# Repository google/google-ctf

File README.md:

# Google CTF

This repository lists most of the challenges used in the Google CTF since 2017, as well as most of the infrastructure that can be used to run them. **IMPORTANT** - The code in the 201x and 202x folders have unfixed security vulnerabilities. These are there on purpose, and running these on real production infrastructure is not safe.

Read more about the Google CTF here: https://security.googleblog.com/2017/06/announcing-google-capture-flag-2017.html

Note this is not an official Google product.

### License

The google-ctf project is available as open source under the terms of the [Apache-2.0 license](https://github.com/google/google-ctf/blob/master/LICENSE).

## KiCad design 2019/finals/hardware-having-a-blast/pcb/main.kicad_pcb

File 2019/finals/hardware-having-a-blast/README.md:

# name: "Having a Blast"

description: Never open strange boxes without a permit. https://youtu.be/_8fBHnH4VNE

The Video above contains no hint or flag that you need to hunt for. This is a time scheduled challenge.

Challenge rules are available https://docs.google.com/document/d/1H1iL3Lq8BtMJRlrBNAAG3CYmMLnWO6IFaZPt1xe8dxI/edit?usp=sharing

# flag: "CTF{k33p-t4k1ng-pl3as3}"

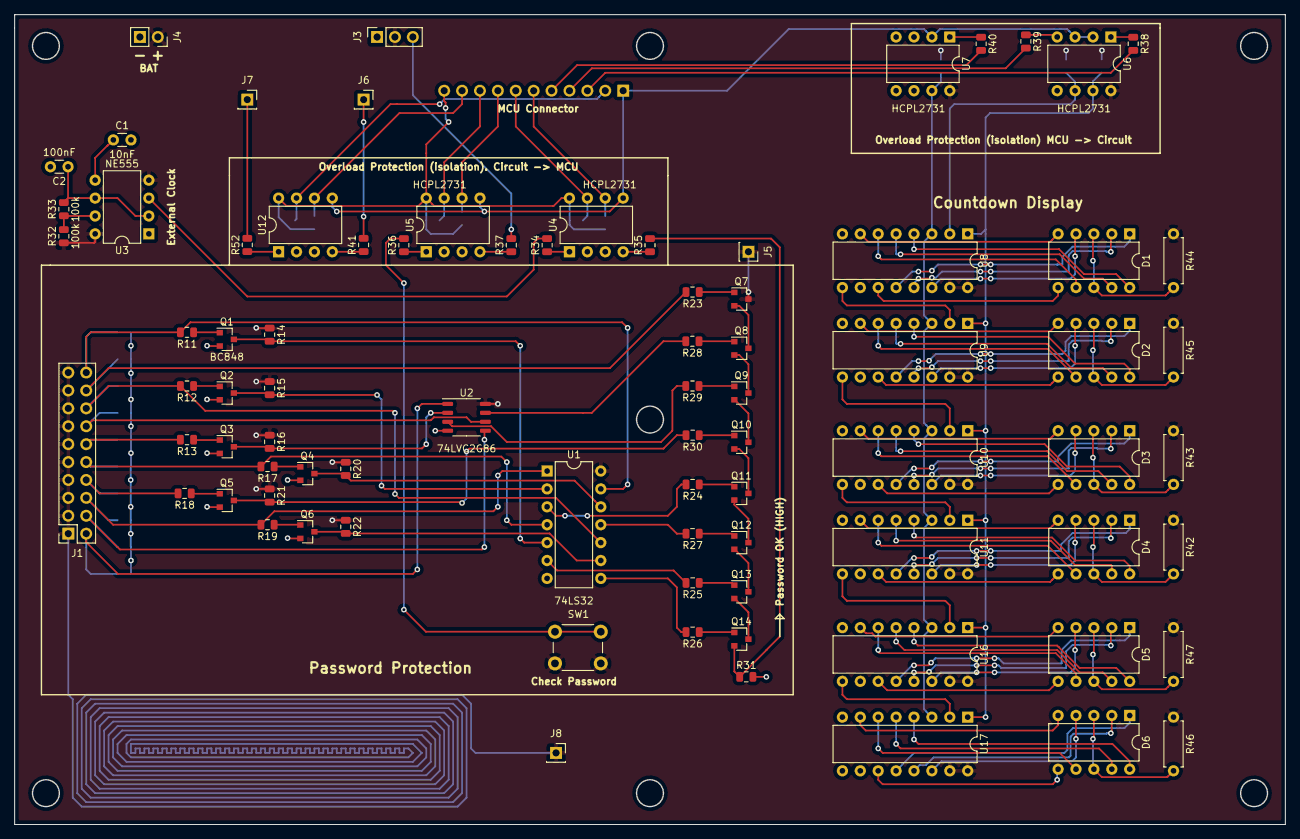
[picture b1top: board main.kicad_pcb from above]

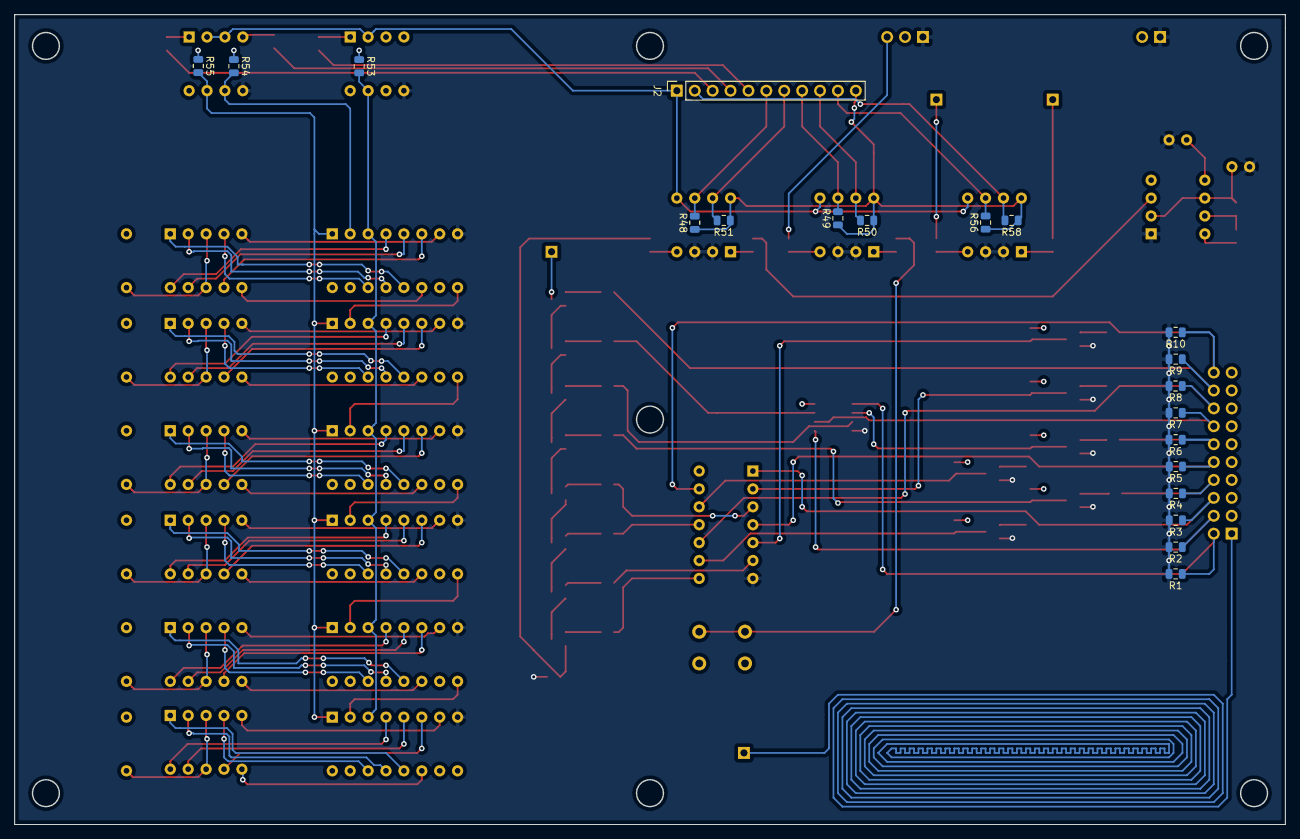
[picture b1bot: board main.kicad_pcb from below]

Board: 4 copper layers, 180.3 x 114.9 mm, 102 parts (20 on the bottom side), 136 nets.

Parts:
C1: 10nF; C_Disc_D3.0mm_W1.6mm_P2.50mm
C2: 100nF; C_Disc_D3.0mm_W1.6mm_P2.50mm
D1, D2, D3, D4, D5, D6: TDSR1050; DIP-10_W7.62mm
J1: Conn_02x10_Odd_Even; PinSocket_2x10_P2.54mm_Vertical
J2: Conn_01x11; PinSocket_1x11_P2.54mm_Vertical
J3: Conn_01x03; PinSocket_1x03_P2.54mm_Vertical
J4: Conn_01x02_Male; PinSocket_1x02_P2.54mm_Vertical
J5, J6, J7, J8: Conn_01x01_Male; PinSocket_1x01_P2.54mm_Vertical
Q1, Q2, Q3, Q4, Q5, Q6, Q7, Q8, Q9, Q10, Q11, Q12, Q13, Q14: BC848; SOT-23
R1, R2, R3, R4, R5, R6, R7, R8, R9, R10, R11, R12, R13, R17, R18, R19, R23, R24, R25, R26, R27, R28, R29, R30: 10k; R_0805_2012Metric
R14, R15, R16, R20, R21, R22, R31, R48, R49, R50, R51, R53, R54, R55, R56, R58: 1k; R_0805_2012Metric
R32, R33: 100k; R_0805_2012Metric
R34, R35, R36, R37, R38, R39, R40, R41, R52: 510; R_0805_2012Metric
R42, R43, R44, R45, R46, R47: 3k; R_Axial_DIN0207_L6.3mm_D2.5mm_P7.62mm_Horizontal
SW1: SW_Push; SW_PUSH_6mm
U1: 74LS32; DIP-14_W7.62mm
U2: 74LVC2G86; SSOP-8_3.9x5.05mm_P1.27mm
U3: NE555; DIP-8_W7.62mm
U4, U5, U6, U7, U12: HCPL2731; DIP-8_W7.62mm
U8, U9, U10, U11, U16, U17: CD4094B; DIP-16_W7.62mm

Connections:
/A0: J1.2, R1.1, U2.1
/A1: J1.4, R2.1, U2.5
/A2: J1.6, R3.1, R19.2, U1.1
/A3: J1.8, R4.1, R18.2
/A4: J1.10, R5.1, R17.2, U1.4
/B0: J1.12, R6.1, R13.2
/B1: J1.14, R7.1, U2.6
/B2: J1.16, R8.1, R12.2, U1.10
/B3: J1.18, R9.1, R23.2
/B4: J1.20, R10.1, R11.2, U1.13
/MCU_GND: J2.1, U4.5, U5.5, U6.2, U6.3, U7.2, U12.5
/MCU_VCC: J2.11, R48.1, R49.1, R50.1, R51.1, R56.1, R58.1, U4.8, U5.8, U12.8
/SevenSegments/Clock: R53.2, U7.7, U8.3, U9.3, U10.3, U11.3, U16.3, U17.3
/SevenSegments/Data: R54.2, U6.6, U8.2
/SevenSegments/Strobe: R55.2, U6.7, U8.1, U9.1, U10.1, U11.1, U16.1, U17.1
/logicIC/LogicOK: Q14.2, R31.1, R35.2
/logicIC/_40: R29.2, U2.3
/logicIC/_45: R28.2, U2.7
/logicIC/~A2: Q6.3, R22.2, U1.9
/logicIC/~A3: Q5.3, R21.2, R30.2
/logicIC/~A4: Q4.3, R20.2, U1.12
/logicIC/~B0: Q3.3, R16.2, U2.2
/logicIC/~B2: Q2.3, R15.2, U1.2
/logicIC/~B4: Q1.3, R14.2, U1.5
/wire_check: J7.1, R52.2
/wire_check2: J6.1, R41.2
GND: C1.2, C2.2, J3.1, J4.2, Q1.2, Q2.2, Q3.2, Q4.2, Q5.2, Q6.2, R1.2, R2.2, R3.2, R4.2, R5.2, R6.2, R7.2, R8.2, R9.2, R10.2, R31.2, U1.7, U2.4, U3.1, U4.2, U4.3, U5.2, U5.3, U6.5, U7.5, U8.8, U9.8, U10.8, U11.8, U12.2, U12.3, U16.8, U17.8
unnamed: C1.1, U3.5
unnamed: C2.1, R33.2, U3.2, U3.6
unnamed: D1.1, U8.12
unnamed: D1.2, U8.13
unnamed: D1.3, D1.8, R44.2
unnamed: D1.4, U8.14
unnamed: D1.5, U8.7
unnamed: D1.6, U8.11
unnamed: D1.7, U8.6
unnamed: D1.9, U8.5
unnamed: D1.10, U8.4
unnamed: D2.1, U9.12
unnamed: D2.2, U9.13
unnamed: D2.3, D2.8, R45.2
unnamed: D2.4, U9.14
unnamed: D2.5, U9.7
unnamed: D2.6, U9.11
unnamed: D2.7, U9.6
unnamed: D2.9, U9.5
unnamed: D2.10, U9.4
unnamed: D3.1, U10.12
unnamed: D3.2, U10.13
unnamed: D3.3, D3.8, R43.2
unnamed: D3.4, U10.14
unnamed: D3.5, U10.7
unnamed: D3.6, U10.11
unnamed: D3.7, U10.6
unnamed: D3.9, U10.5
unnamed: D3.10, U10.4
unnamed: D4.1, U11.12
unnamed: D4.2, U11.13
unnamed: D4.3, D4.8, R42.2
unnamed: D4.4, U11.14
unnamed: D4.5, U11.7
unnamed: D4.6, U11.11
unnamed: D4.7, U11.6
unnamed: D4.9, U11.5
unnamed: D4.10, U11.4
unnamed: D5.1, U16.12
unnamed: D5.2, U16.13
unnamed: D5.3, D5.8, R47.2
unnamed: D5.4, U16.14
unnamed: D5.5, U16.7
unnamed: D5.6, U16.11
unnamed: D5.7, U16.6
unnamed: D5.9, U16.5
unnamed: D5.10, U16.4
unnamed: D6.1, U17.12
unnamed: D6.2, U17.13
unnamed: D6.3, D6.8, R46.2
unnamed: D6.4, U17.14
unnamed: D6.5, U17.7
unnamed: D6.6, U17.11
unnamed: D6.7, U17.6
unnamed: D6.9, U17.5
unnamed: D6.10, U17.4
unnamed: J2.2, R58.2, U12.7
unnamed: J2.3, R38.2
unnamed: J2.4, R39.2
unnamed: J2.5, R40.2
unnamed: J2.6, R48.2, U4.6
unnamed: J2.7, R51.2, U4.7
unnamed: J2.8, R49.2, U5.6
unnamed: J2.9, R50.2, U5.7
unnamed: J2.10, R56.2, U12.6
unnamed: J3.3, R37.2
unnamed: Q1.1, R11.1
unnamed: Q2.1, R12.1
unnamed: Q3.1, R13.1
unnamed: Q4.1, R17.1
unnamed: Q5.1, R18.1
unnamed: Q6.1, R19.1
unnamed: Q7.1, R23.1
unnamed: Q7.2, Q8.3
unnamed: Q8.1, R28.1
unnamed: Q8.2, Q9.3
unnamed: Q9.1, R29.1
unnamed: Q10.1, R30.1
unnamed: Q10.2, Q11.3
unnamed: Q9.2, Q10.3
unnamed: Q11.1, R24.1
unnamed: Q11.2, Q12.3
unnamed: Q12.1, R27.1
unnamed: Q12.2, Q13.3
unnamed: Q13.1, R25.1
unnamed: Q13.2, Q14.3
unnamed: Q14.1, R26.1
unnamed: R24.2, U1.3
unnamed: R25.2, U1.6
unnamed: R26.2, U1.8
unnamed: R27.2, U1.11
unnamed: R32.2, R33.1, U3.7
unnamed: R34.1, U4.1
unnamed: R34.2, U3.3
unnamed: R35.1, U4.4
unnamed: R36.1, U5.1
unnamed: R36.2, SW1.2
unnamed: R37.1, U5.4
unnamed: R38.1, U6.1
unnamed: R39.1, U6.4
unnamed: R40.1, U7.1
unnamed: R41.1, U12.4
unnamed: R52.1, U12.1
unnamed: U8.9, U9.2
unnamed: U9.9, U10.2
unnamed: U10.9, U11.2
unnamed: U11.9, U16.2
unnamed: U16.9, U17.2
VCC: J1.1, J1.3, J1.5, J1.7, J1.9, J1.11, J1.13, J1.15, J1.17, J1.19, J3.2, J4.1, J5.1, J8.1, Q7.3, R14.1, R15.1, R16.1, R20.1, R21.1, R22.1, R32.1, R42.1, R43.1, R44.1, R45.1, R46.1, R47.1, R53.1, R54.1, R55.1, SW1.1, U1.14, U2.8, U3.4, U3.8, U6.8, U7.8, U8.15, U8.16, U9.15, U9.16, U10.15, U10.16, U11.15, U11.16, U16.15, U16.16, U17.15, U17.16

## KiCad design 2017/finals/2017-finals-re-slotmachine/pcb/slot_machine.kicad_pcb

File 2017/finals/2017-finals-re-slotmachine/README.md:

{

# name: Slot Machine 1
# description: We found some spare slot machines that are used at GenericCasinoCompany. We believe that there is some hidden treasure inside, can you find it?

# flag: CTF{5UP3R_53CR37_BTN_C0MB1N4710N}"

}

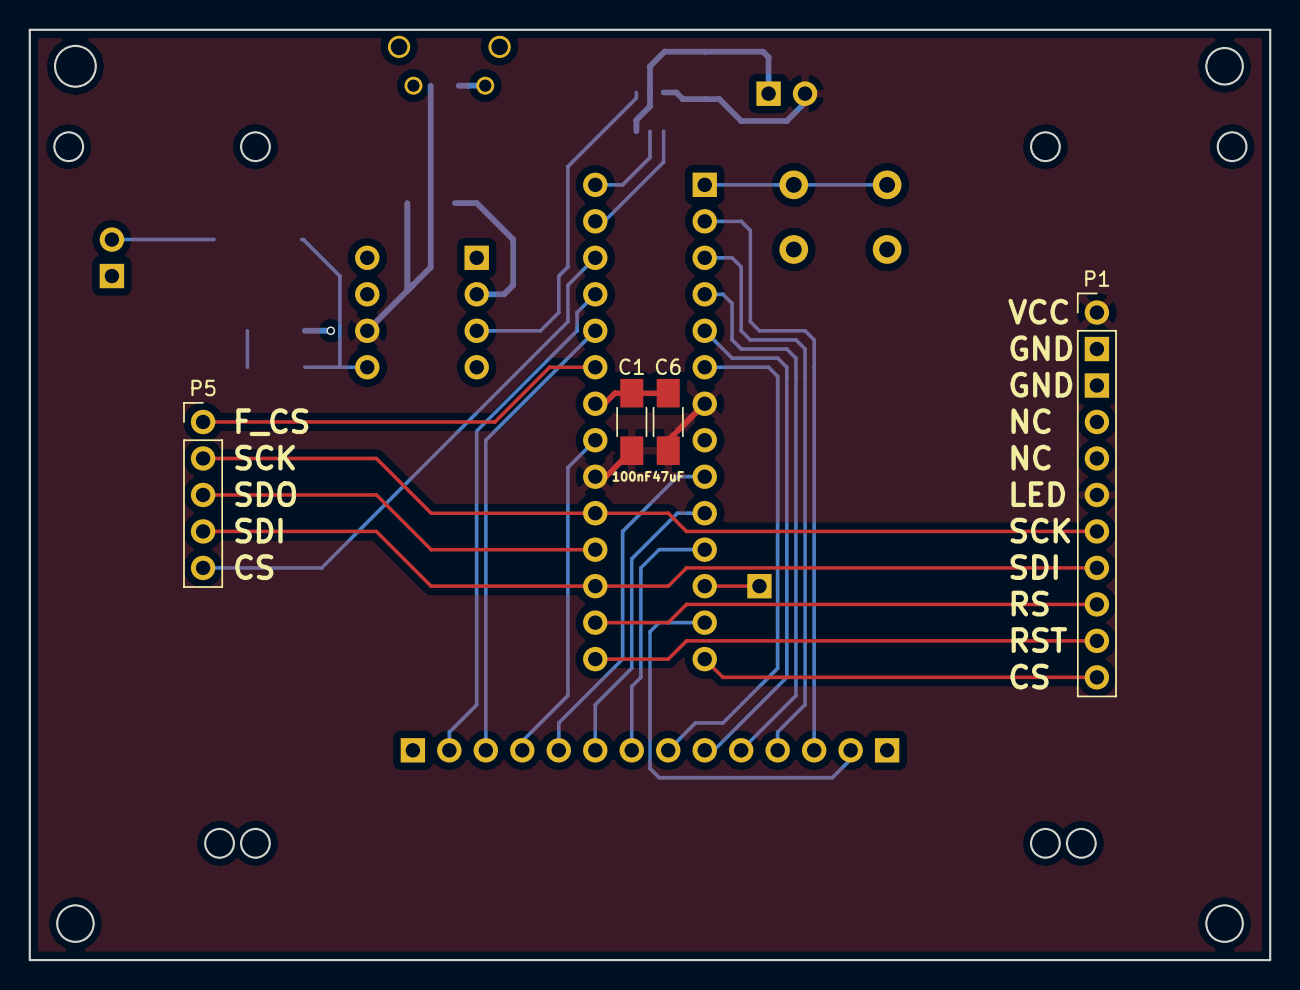
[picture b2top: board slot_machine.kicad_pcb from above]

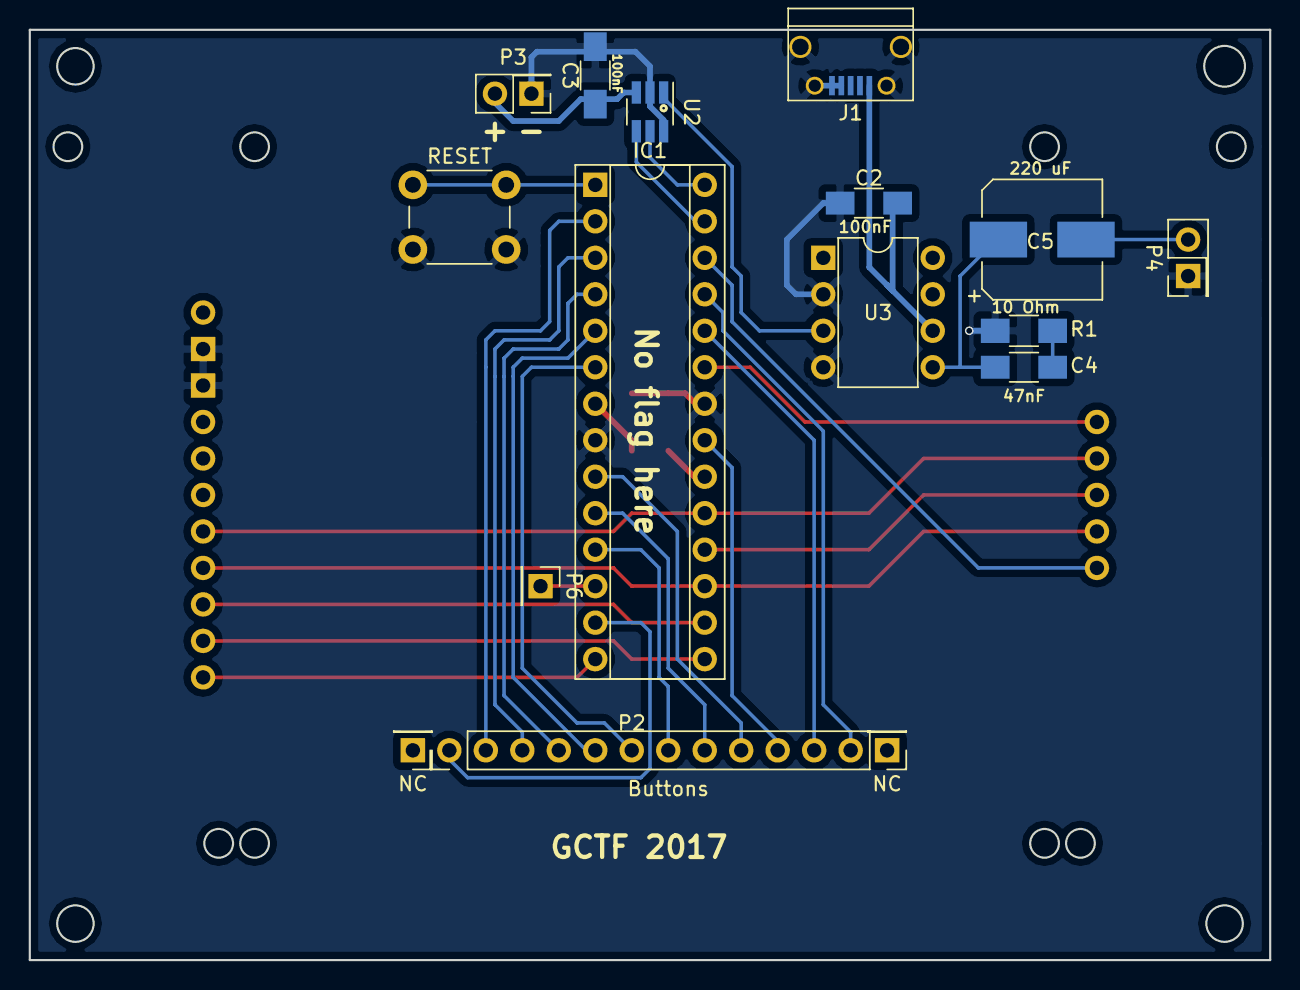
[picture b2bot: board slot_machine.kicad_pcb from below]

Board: 2 copper layers, 86.4 x 64.8 mm, 20 parts (16 on the bottom side), 30 nets.

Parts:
C1, C2, C3: 100nF; C_1206_HandSoldering
C4: 47nF; C_1206_HandSoldering
C5: 220 uF; CP_Elec_8x5.4
C6: 47uF; C_1206_HandSoldering
IC1: ATTINY48-P; DIP-28_W7.62mm_Socket
J1: USB; USB_Micro-B
NC: CONN_1; Pin_Header_Straight_1x01_Pitch2.54mm
NC#2: CONN_1; Pin_Header_Straight_1x01_Pitch2.54mm
P1: CONN_DSPL; Socket_Strip_Straight_1x11_Pitch2.54mm
P2: Buttons; Pin_Header_Straight_1x12_Pitch2.54mm
P3: CONN_2; Pin_Header_Straight_2x01_Pitch2.54mm
P4: CONN_SPEAKER; Pin_Header_Straight_2x01_Pitch2.54mm
P5: CONN_CARD; Socket_Strip_Straight_1x05_Pitch2.54mm
P6: CONN_1; Socket_Strip_Straight_1x01_Pitch2.54mm
R1: 10 Ohm; R_1206_HandSoldering
RESET: SW_PUSH; SW_PUSH_6mm
U2: MCP4725; SOT-23-6_Handsoldering
U3: LM386; DIP-8_W7.62mm

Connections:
/bet5: IC1.2, P2.2
/deal_draw: IC1.5, P2.5
/hold4: IC1.3, P2.3
/hold5: IC1.13, P2.1
/maxbet: IC1.4, P2.4
CS_CARD: IC1.26, P5.5
CS_DSPL: IC1.14, P1.11
CS_F: IC1.23, P5.1
DSPL_RST: IC1.15, P1.10
GND: C1.2, C2.1, C3.2, C6.2, IC1.8, IC1.22, J1.4, J1.5, J1.6, P1.2, P1.3, P3.1, P4.1, R1.1, RESET.2, U2.2, U2.6, U3.2, U3.4
unnamed: C4.1, C5.1, U3.5
unnamed: C4.2, R1.2
unnamed: C5.2, P4.2
unnamed: IC1.1, RESET.1
unnamed: IC1.12, P6.1
unnamed: U2.1, U3.3
RS: IC1.16, P1.9
SCK: IC1.19, P1.7, P5.2
SCL: IC1.28, U2.5
SDA: IC1.27, U2.4
SDI: IC1.17, P1.8, P5.4
SDO: IC1.18, P5.3
VCC: C1.1, C2.2, C3.1, C6.1, IC1.7, IC1.20, J1.1, P1.1, P1.6, P3.2, U2.3, U3.6
btn_bet/hold2: IC1.10, P2.8
btn_max_bet/common__: IC1.11, P2.7
btn_mute/mute: IC1.9, P2.9
btn_player/points: IC1.24, P2.11
btn_points/hold1: IC1.21, P2.10
btn_spin/hold3: IC1.6, P2.6
mostly_common: IC1.25, P2.12

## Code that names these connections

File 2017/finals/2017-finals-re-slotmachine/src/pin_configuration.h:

/*
 * Copyright 2018 Google LLC
 *
 * Licensed under the Apache License, Version 2.0 (the "License");
 * you may not use this file except in compliance with the License.
 * You may obtain a copy of the License at
 *
 *      http://www.apache.org/licenses/LICENSE-2.0
 *
 * Unless required by applicable law or agreed to in writing, software
 * distributed under the License is distributed on an "AS IS" BASIS,
 * WITHOUT WARRANTIES OR CONDITIONS OF ANY KIND, either express or implied.
 * See the License for the specific language governing permissions and
 * limitations under the License.
 */



#pragma once
#include <avr/io.h>

// Port B
namespace PortB {
constexpr uint8_t CS_DSPL = 1 << PB0;
constexpr uint8_t DSPL_RESET = 1 << PB1;
constexpr uint8_t RS = 1 << PB2;
constexpr uint8_t SS = 1 << PB2;
constexpr uint8_t MOSI = 1 << PB3;
constexpr uint8_t MISO = 1 << PB4;
constexpr uint8_t SCK = 1 << PB5;
constexpr uint8_t BTN_0 = 1 << PB6;
constexpr uint8_t BTN_1 = 1 << PB7;
} // namespace PortB

// Port C
namespace PortC {
constexpr uint8_t CS_F = 1 << PC0;
constexpr uint8_t BTN_2 = 1 << PC1;
constexpr uint8_t BTN_3 = 1 << PC2;
constexpr uint8_t CS_CARD = 1 << PC3;
constexpr uint8_t I2C_DATA = 1 << PC4;
constexpr uint8_t I2C_CLK = 1 << PC5;
constexpr uint8_t BTN_4 = 1 << PC7;
} // namespace PortC

// Port D
namespace PortD {
constexpr uint8_t BTN_5 = 1 << PD0;
constexpr uint8_t BTN_6 = 1 << PD1;
constexpr uint8_t BTN_7 = 1 << PD2;
constexpr uint8_t BTN_8 = 1 << PD3;
constexpr uint8_t BTN_9 = 1 << PD4;
constexpr uint8_t BTN_10 = 1 << PD5;
constexpr uint8_t BTN_11 = 1 << PD7;
constexpr uint8_t EXTENSION_1 = 1 << PD6;
constexpr uint8_t EXTENSION_2 = 1 << PD7;
} // namespace PortD

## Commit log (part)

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2023-06-25 Release gCTF 2023 challenges and write-ups
2023-08-04 Bump semver from 6.3.0 to 6.3.1 in /2020/quals/web-pasteurize/app
    Bumps [semver](https://github.com/npm/node-semver) from 6.3.0 to 6.3.1.
    - [Release notes](https://github.com/npm/node-semver/releases)
    - [Changelog](https://github.com/npm/node-semver/blob/v6.3.1/CHANGELOG.md)
    - [Commits](https://github.com/npm/node-semver/compare/v6.3.0...v6.3.1)
    ---
    updated-dependencies:
2023-08-04 Bump semver from 6.3.0 to 6.3.1 in /2020/quals/web-log-me-in/app
    Bumps [semver](https://github.com/npm/node-semver) from 6.3.0 to 6.3.1.
    - [Release notes](https://github.com/npm/node-semver/releases)
    - [Changelog](https://github.com/npm/node-semver/blob/v6.3.1/CHANGELOG.md)
    - [Commits](https://github.com/npm/node-semver/compare/v6.3.0...v6.3.1)
    ---
    updated-dependencies:
2023-08-15 Bump flask from 0.12.1 to 2.2.5 in /2017/quals/2017-misc-mindreader/app (#79)
    Bumps [flask](https://github.com/pallets/flask) from 0.12.1 to 2.2.5.
    - [Release notes](https://github.com/pallets/flask/releases)
    - [Changelog](https://github.com/pallets/flask/blob/main/CHANGES.rst)
    - [Commits](https://github.com/pallets/flask/compare/0.12.1...2.2.5)
    ---
    updated-dependencies:
2023-08-28 Bump flask in /2023/quals/web-under-construction/challenge/flask
    Bumps [flask](https://github.com/pallets/flask) from 2.2.3 to 2.2.5.
    - [Release notes](https://github.com/pallets/flask/releases)
    - [Changelog](https://github.com/pallets/flask/blob/main/CHANGES.rst)
    - [Commits](https://github.com/pallets/flask/compare/2.2.3...2.2.5)
    ---
    updated-dependencies:
2023-09-22 - New release (#98)
2023-10-11 Bump golang.org/x/net in /2023/quals/misc-totallynotbruteforce/solution
    Bumps [golang.org/x/net](https://github.com/golang/net) from 0.10.0 to 0.17.0.
    - [Commits](https://github.com/golang/net/compare/v0.10.0...v0.17.0)
    ---
    updated-dependencies:
    - dependency-name: golang.org/x/net
    dependency-type: indirect
2023-10-31 Add license in README.md
2024-03-13 Bump google.golang.org/protobuf in /2021/quals/crypto-tonality/challenge
    Bumps google.golang.org/protobuf from 1.26.0 to 1.33.0.
    ---
    updated-dependencies:
    - dependency-name: google.golang.org/protobuf
    dependency-type: direct:production
    ...
2024-03-27 Bump express from 4.17.1 to 4.19.2 in /2021/hackceler8/game 2
    Bumps [express](https://github.com/expressjs/express) from 4.17.1 to 4.19.2.
    - [Release notes](https://github.com/expressjs/express/releases)
    - [Changelog](https://github.com/expressjs/express/blob/master/History.md)
    - [Commits](https://github.com/expressjs/express/compare/4.17.1...4.19.2)
    ---
    updated-dependencies:
2024-04-01 Bump django from 2.2.5 to 3.2.25 in /2019/finals/web-gphotos-finals/app
    Bumps [django](https://github.com/django/django) from 2.2.5 to 3.2.25.
    - [Commits](https://github.com/django/django/compare/2.2.5...3.2.25)
    ---
    updated-dependencies:
    - dependency-name: django
    dependency-type: direct:production
2024-04-19 Bump golang.org/x/net
    Bumps [golang.org/x/net](https://github.com/golang/net) from 0.10.0 to 0.23.0.
    - [Commits](https://github.com/golang/net/compare/v0.10.0...v0.23.0)
    ---
    updated-dependencies:
    - dependency-name: golang.org/x/net
    dependency-type: indirect
2024-07-13 bump the pip group across 9 directories with 12 updates
    ---
    updated-dependencies:
    - dependency-name: gunicorn
    dependency-type: direct:production
    dependency-group: pip
    - dependency-name: flask
2024-07-21 Bump browserify-sign in /2022/quals/web-gpushop/paymeflare/challenge/src (#19)
    Bumps [browserify-sign](https://github.com/crypto-browserify/browserify-sign) from 4.2.1 to 4.2.2.
    - [Changelog](https://github.com/browserify/browserify-sign/blob/main/CHANGELOG.md)
    - [Commits](https://github.com/crypto-browserify/browserify-sign/compare/v4.2.1...v4.2.2)
    ---
    updated-dependencies:
    - dependency-name: browserify-sign
2024-07-21 Bump golang.org/x/net (#31)
    Bumps [golang.org/x/net](https://github.com/golang/net) from 0.0.0-20211015210444-4f30a5c0130f to 0.17.0.
    - [Commits](https://github.com/golang/net/commits/v0.17.0)
    ---
    updated-dependencies:
    - dependency-name: golang.org/x/net
    dependency-type: indirect
2024-07-21 Bump mongodb and mongoose in /2023/quals/web-noteninja/challenge/src (#45)
    Bumps [mongodb](https://github.com/mongodb/node-mongodb-native) to 5.8.1 and updates ancestor dependency [mongoose](https://github.com/Automattic/mongoose). These dependencies need to be updated toge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
    Updates `mongodb` from 5.3.0 to 5.8.1
    - [Release notes](https://github.com/mongodb/node-mongodb-native/releases)
    - [Changelog](https://github.com/mongodb/node-mongodb-native/blob/v5.8.1/HISTORY.md)
    - [Commits](https://github.com/mongodb/node-mongodb-native/compare/v5.3.0...v5.8.1)
    Updates `mongoose` from 7.1.0 to 7.5.0
2024-07-21 Bump google.golang.org/grpc (#73)
    Bumps [google.golang.org/grpc](https://github.com/grpc/grpc-go) from 1.54.0 to 1.56.3.
    - [Release notes](https://github.com/grpc/grpc-go/releases)
    - [Commits](https://github.com/grpc/grpc-go/compare/v1.54.0...v1.56.3)
    ---
    updated-dependencies:
    - dependency-name: google.golang.org/grpc
2024-07-21 Bump express from 4.17.1 to 4.19.2 in /2020/quals/web-pasteurize/app (#87)
    Bumps [express](https://github.com/expressjs/express) from 4.17.1 to 4.19.2.
    - [Release notes](https://github.com/expressjs/express/releases)
    - [Changelog](https://github.com/expressjs/express/blob/master/History.md)
    - [Commits](https://github.com/expressjs/express/compare/4.17.1...4.19.2)
    ---
    updated-dependencies:
2024-07-21 Move codec to the right place (#100)
    'ascii' codec can't decode byte 0xe2 in position 8013: ordinal not in range(128)
2024-07-21 Bump express in /2022/quals/web-gpushop/paymeflare/challenge/src (#117)
    Bumps [express](https://github.com/expressjs/express) from 4.17.1 to 4.19.2.
    - [Release notes](https://github.com/expressjs/express/releases)
    - [Changelog](https://github.com/expressjs/express/blob/master/History.md)
    - [Commits](https://github.com/expressjs/express/compare/4.17.1...4.19.2)
    ---
    updated-dependencies:
2024-07-21 Bump flask in /2023/quals/web-under-construction/challenge/flask (#133)
    Bumps [flask](https://github.com/pallets/flask) from 2.2.3 to 2.2.5.
    - [Release notes](https://github.com/pallets/flask/releases)
    - [Changelog](https://github.com/pallets/flask/blob/main/CHANGES.rst)
    - [Commits](https://github.com/pallets/flask/compare/2.2.3...2.2.5)
    ---
    updated-dependencies:
2024-07-21 Bump express in /2022/quals/web-gpushop/paymeflare/challenge/src (#153)
    Bumps [express](https://github.com/expressjs/express) from 4.17.1 to 4.19.2.
    - [Release notes](https://github.com/expressjs/express/releases)
    - [Changelog](https://github.com/expressjs/express/blob/master/History.md)
    - [Commits](https://github.com/expressjs/express/compare/4.17.1...4.19.2)
    ---
    updated-dependencies:
2024-07-21 Bump sqlparse from 0.3.0 to 0.5.0 in /2019/finals/web-gphotos-finals/app (#164)
    Bumps [sqlparse](https://github.com/andialbrecht/sqlparse) from 0.3.0 to 0.5.0.
    - [Changelog](https://github.com/andialbrecht/sqlparse/blob/master/CHANGELOG)
    - [Commits](https://github.com/andialbrecht/sqlparse/compare/0.3.0...0.5.0)
    ---
    updated-dependencies:
    - dependency-name: sqlparse
2024-07-21 Bump express from 4.17.1 to 4.19.2 in /2020/quals/web-pasteurize/app (#178)
    Bumps [express](https://github.com/expressjs/express) from 4.17.1 to 4.19.2.
    - [Release notes](https://github.com/expressjs/express/releases)
    - [Changelog](https://github.com/expressjs/express/blob/master/History.md)
    - [Commits](https://github.com/expressjs/express/compare/4.17.1...4.19.2)
    ---
    updated-dependencies:
2024-07-21 Bump golang.org/x/net (#233)
    Bumps [golang.org/x/net](https://github.com/golang/net) from 0.0.0-20211015210444-4f30a5c0130f to 0.17.0.
    - [Commits](https://github.com/golang/net/commits/v0.17.0)
    ---
    updated-dependencies:
    - dependency-name: golang.org/x/net
    dependency-type: indirect
2024-07-21 Bump browserify-sign in /2022/quals/web-gpushop/paymeflare/challenge/src (#246)
    Bumps [browserify-sign](https://github.com/crypto-browserify/browserify-sign) from 4.2.1 to 4.2.2.
    - [Changelog](https://github.com/browserify/browserify-sign/blob/main/CHANGELOG.md)
    - [Commits](https://github.com/crypto-browserify/browserify-sign/compare/v4.2.1...v4.2.2)
    ---
    updated-dependencies:
    - dependency-name: browserify-sign
2024-07-21 Bump socket2 from 0.3.12 to 0.3.19 in /2020/quals/pwn-tracing (#269)
    Bumps [socket2](https://github.com/rust-lang/socket2) from 0.3.12 to 0.3.19.
    - [Release notes](https://github.com/rust-lang/socket2/releases)
    - [Changelog](https://github.com/rust-lang/socket2/blob/master/CHANGELOG.md)
    - [Commits](https://github.com/rust-lang/socket2/compare/0.3.12...v0.3.19)
    ---
    updated-dependencies:
2024-07-21 Bump socket2 from 0.3.12 to 0.3.19 in /2020/quals/pwn-tracing (#296)
    Bumps [socket2](https://github.com/rust-lang/socket2) from 0.3.12 to 0.3.19.
    - [Release notes](https://github.com/rust-lang/socket2/releases)
    - [Changelog](https://github.com/rust-lang/socket2/blob/master/CHANGELOG.md)
    - [Commits](https://github.com/rust-lang/socket2/compare/0.3.12...v0.3.19)
    ---
    updated-dependencies:
2024-07-21 Move codec to the right place (#316)
    'ascii' codec can't decode byte 0xe2 in position 8013: ordinal not in range(128)
2024-07-21 Bump google.golang.org/grpc (#329)
    Bumps [google.golang.org/grpc](https://github.com/grpc/grpc-go) from 1.54.0 to 1.56.3.
    - [Release notes](https://github.com/grpc/grpc-go/releases)
    - [Commits](https://github.com/grpc/grpc-go/compare/v1.54.0...v1.56.3)
    ---
    updated-dependencies:
    - dependency-name: google.golang.org/grpc
2024-08-14 Update license for grandprixheaven artwork
2024-10-03 Change arcade game shebang to support more systems.
2024-10-15 More small fixes to the game engine - prrrrobably the last release before the competition.
    Adding a more proper fix for the startup race condition, fixing arcade system in compat mode updating and pinning deps.
2025-08-31 Bump the npm_and_yarn group across 29 directories with 26 updates
    Bumps the npm_and_yarn group with 1 update in the /2018/quals/misc-bookshelf/app directory: [multer](https://github.com/expressjs/multer).
    Bumps the npm_and_yarn group with 3 updates in the /2018/quals/web-cat-chat/app directory: [brace-expansion](https://github.com/juliangruber/brace-expansion), [path-to-regexp](https://github.com/pill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
    Bumps the npm_and_yarn group with 5 updates in the /2020/quals/web-littlethings-fixed/app directory:
    | Package | From | To |
    | --- | --- | --- |
    | [brace-expansion](https://github.com/juliangruber/brace-expansion) | `1.1.
